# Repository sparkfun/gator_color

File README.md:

SparkFun gator:color
========================================

[*SparkFun gator:color - COM-14890*](https://www.sparkfun.com/products/14890)

The gator:color a smattering of LEDs into an alligator clippable format for use with micro:bit as well as the gator:bit expansion for micro:bit.

Repository Contents
-------------------
* **/Firmware** - Example code used in the gator:color. While they are compiled HEX codes, you can modify the example code once they are imported into MakeCode editor.
* **/Hardware** - Eagle design files (.brd, .sch)
* **/Production** - Production panel files (.brd)

Documentation
--------------
* **[Hookup Guide](https://learn.sparkfun.com/tutorials/gatorcolor-protosnap-hookup-guide)** - Basic hookup guide for the gator:color.

Product Versions
----------------
* [COM-14890](https://www.sparkfun.com/products/14890)- The gator:color allows you to gator-clip to LED's.

License Information
-------------------

This product is _**open source**_! 

Please review the LICENSE.md file for license information. 

If you have any questions or concerns on licensing, please contact techsupport@sparkfun.com.

Distributed as-is; no warranty is given.

- Your friends at SparkFun.

_<COLLABORATION CREDIT>_

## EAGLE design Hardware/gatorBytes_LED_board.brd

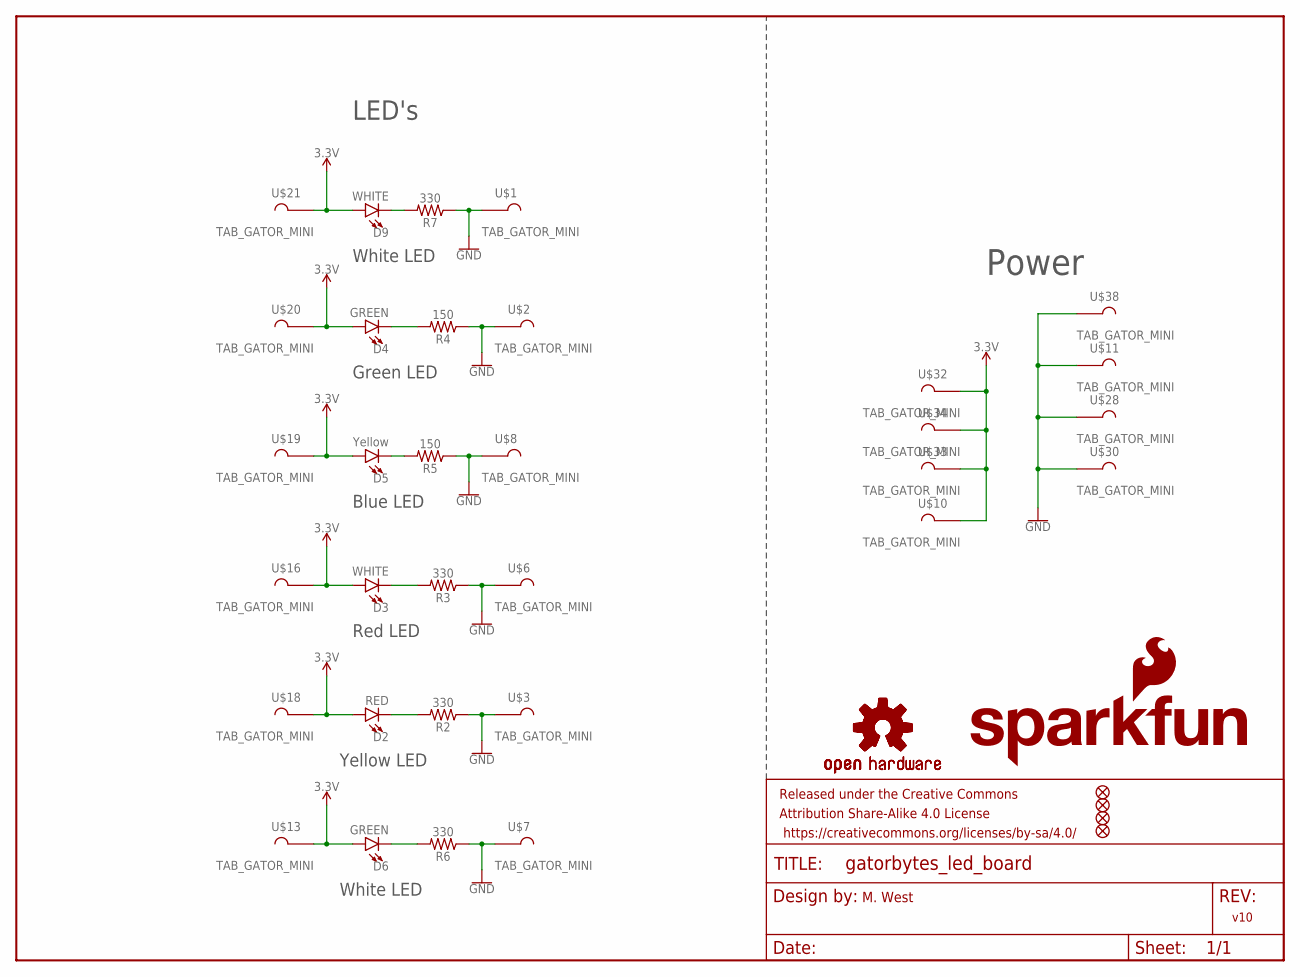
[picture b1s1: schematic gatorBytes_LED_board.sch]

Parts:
D2: RED; LED-1206
D3, D9: WHITE; LED-1206
D4, D6: GREEN; LED-1206
D5: Yellow; LED-1206
FD1, FD2, FD3, FD4: FIDUCIALUFIDUCIAL; FIDUCIAL-MICRO
FRAME1: FRAME-LETTER; CREATIVE_COMMONS
LOGO1: SFE_LOGO_FLAME.1_INCH; SFE_LOGO_FLAME_.1
LOGO2, LOGO15: OSHW-LOGOMINI; OSHW-LOGO-MINI
LOGO16: SFE_LOGO_NAME.1_INCH; SFE_LOGO_NAME_.1
R2, R3, R6, R7: 330; 0603
R4, R5: 150; 0603
U$1, U$2, U$3, U$6, U$7, U$8, U$10, U$11, U$13, U$16, U$18, U$19, U$20, U$21, U$28, U$30, U$32, U$33, U$34, U$38: TAB_GATOR_MINI

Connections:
3.3V: D2.A, D3.A, D4.A, D5.A, D6.A, D9.A, U$10.P1, U$13.P1, U$16.P1, U$18.P1, U$19.P1, U$20.P1, U$21.P1, U$32.P1, U$33.P1, U$34.P1
GND: R2.1, R3.1, R4.1, R5.1, R6.1, R7.1, U$1.P1, U$2.P1, U$3.P1, U$6.P1, U$7.P1, U$8.P1, U$11.P1, U$28.P1, U$30.P1, U$38.P1
unnamed: D2.C, R2.2
unnamed: D3.C, R3.2
unnamed: D4.C, R4.2
unnamed: D5.C, R5.2
unnamed: D6.C, R6.2
unnamed: D9.C, R7.2

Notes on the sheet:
Red LED
Yellow LED
Blue LED
Green LED
White LED
M. West
v10
LED's
Power

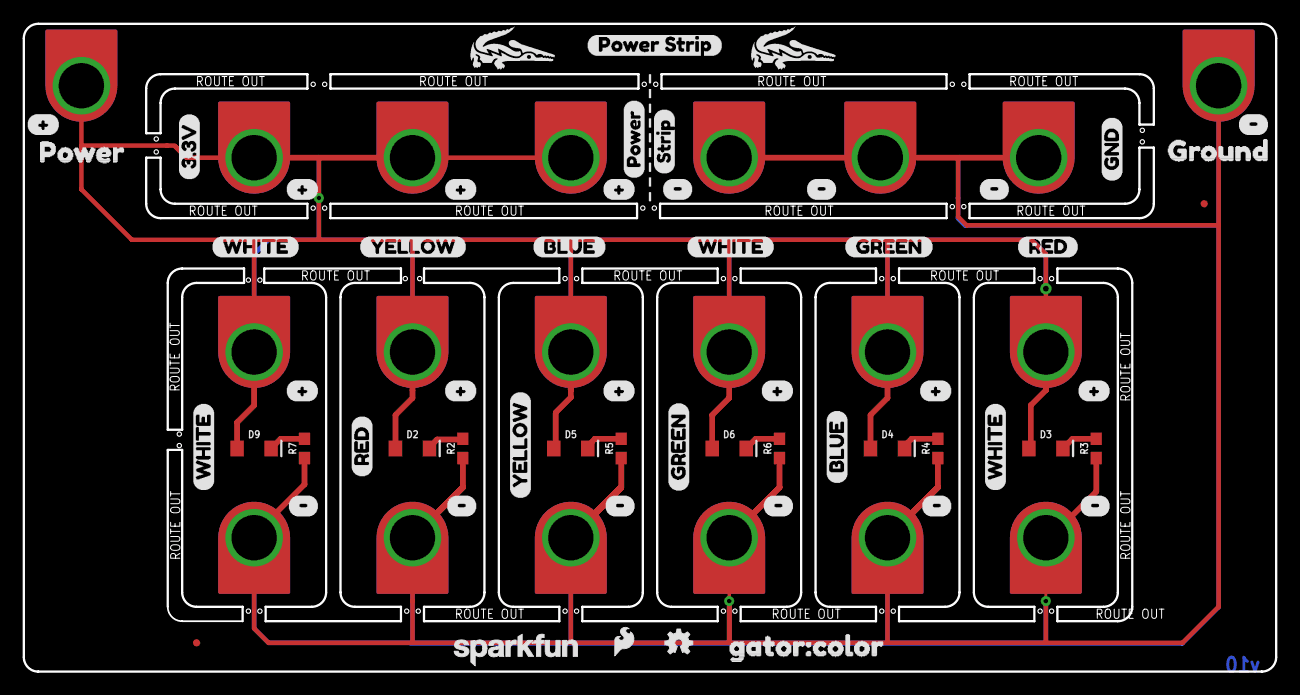
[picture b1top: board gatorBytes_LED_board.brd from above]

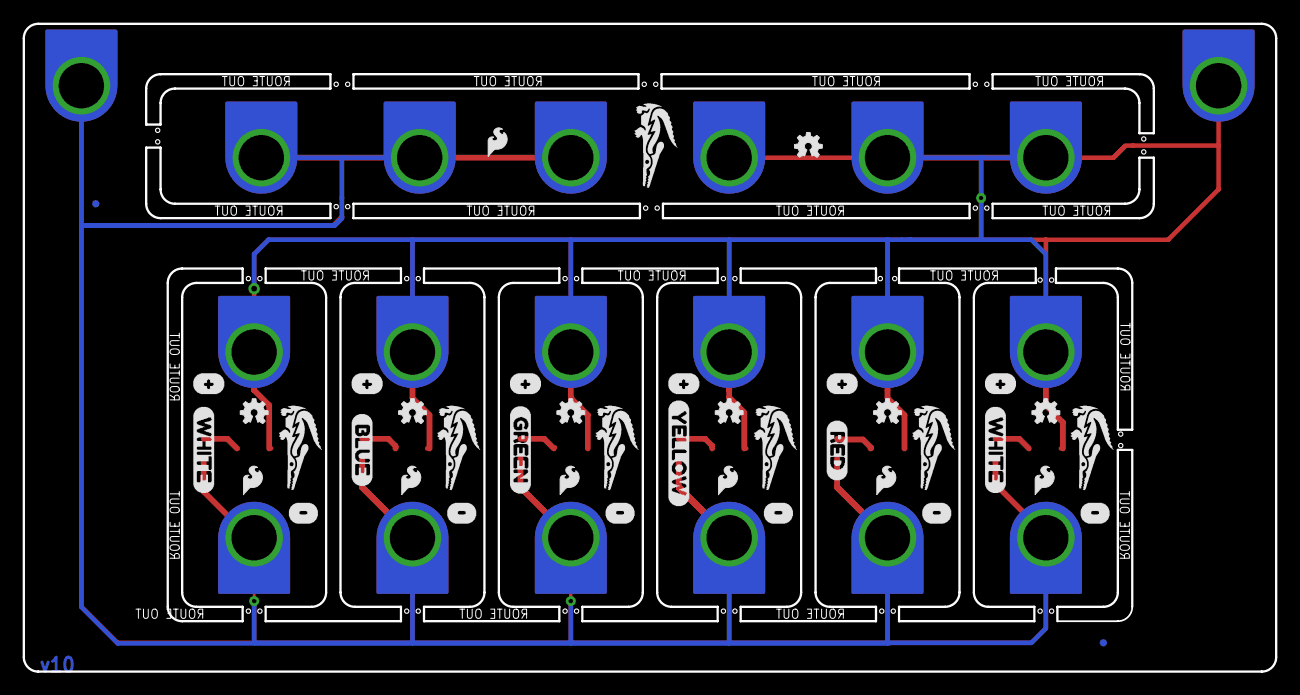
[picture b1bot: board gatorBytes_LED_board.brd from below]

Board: 2 copper layers, 110.5 x 57.1 mm, 122 parts (41 on the bottom side), 8 nets.

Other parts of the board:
LOGO3, LOGO4, LOGO5, LOGO6, LOGO7, LOGO18: OSHW-LOGOMINI; OSHW-LOGO-MINI
LOGO9, LOGO10, LOGO11, LOGO12, LOGO13, LOGO17, LOGO19: SFE_LOGO_FLAME.1_INCH; SFE_LOGO_FLAME_.1
U$4: ORDERING_INSTRUCTIONS
U$5: POWER_STRIP0
U$9: GROUND3
U$12, U$14, U$15, U$53, U$55, U$57, U$60, U$62, U$64, U$77, U$81, U$83, U$84, U$85, U$86, U$87: #8
U$17, U$41, U$42: RED2
U$22, U$23, U$24, U$54, U$56, U$58, U$61, U$63, U$65, U$82, U$89, U$90, U$91, U$92, U$93, U$95: #9
U$25: 3#3V1
U$26: GND0
U$27: POWER1
U$29, U$31, U$50, U$68, U$69, U$70, U$71, U$72, U$73: GATOR#PNG
U$35: STRIP2
U$36, U$37, U$75: BLUE4
U$39, U$40, U$67: GREEN3
U$43: POWER2
U$44, U$45, U$46, U$47, U$78, U$79: WHITE6
U$48, U$49, U$76: YELLOW5
U$51: GATOR#COLOR0

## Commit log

2018-08-23 removing pth
2018-09-12 pre design review
2018-09-12 post checklist changes
2018-09-14 created panel v10
2018-10-18 updating readme
2018-10-18 cleaning repo
2018-10-19 Hookup guide name changed
    Updating link to hookup guide
2019-01-09 gator:color Example Code HEX files
    Add compiled MakeCode example code used with the gator:color

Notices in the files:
parts and their libraries:
SparkFun-LED: Licensing: Creative Commons ShareAlike 4.0 International - https://creativecommons.org/licenses/by-sa/4.0
SparkFun-Aesthetics: Released under the Creative Commons Attribution Share-Alike 4.0 License
SparkFun-Aesthetics: https://creativecommons.org/licenses/by-sa/4.0
